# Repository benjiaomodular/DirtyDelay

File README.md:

# DirtyDelay
A PT2399-based delay guitar pedal with an overdrive at the output

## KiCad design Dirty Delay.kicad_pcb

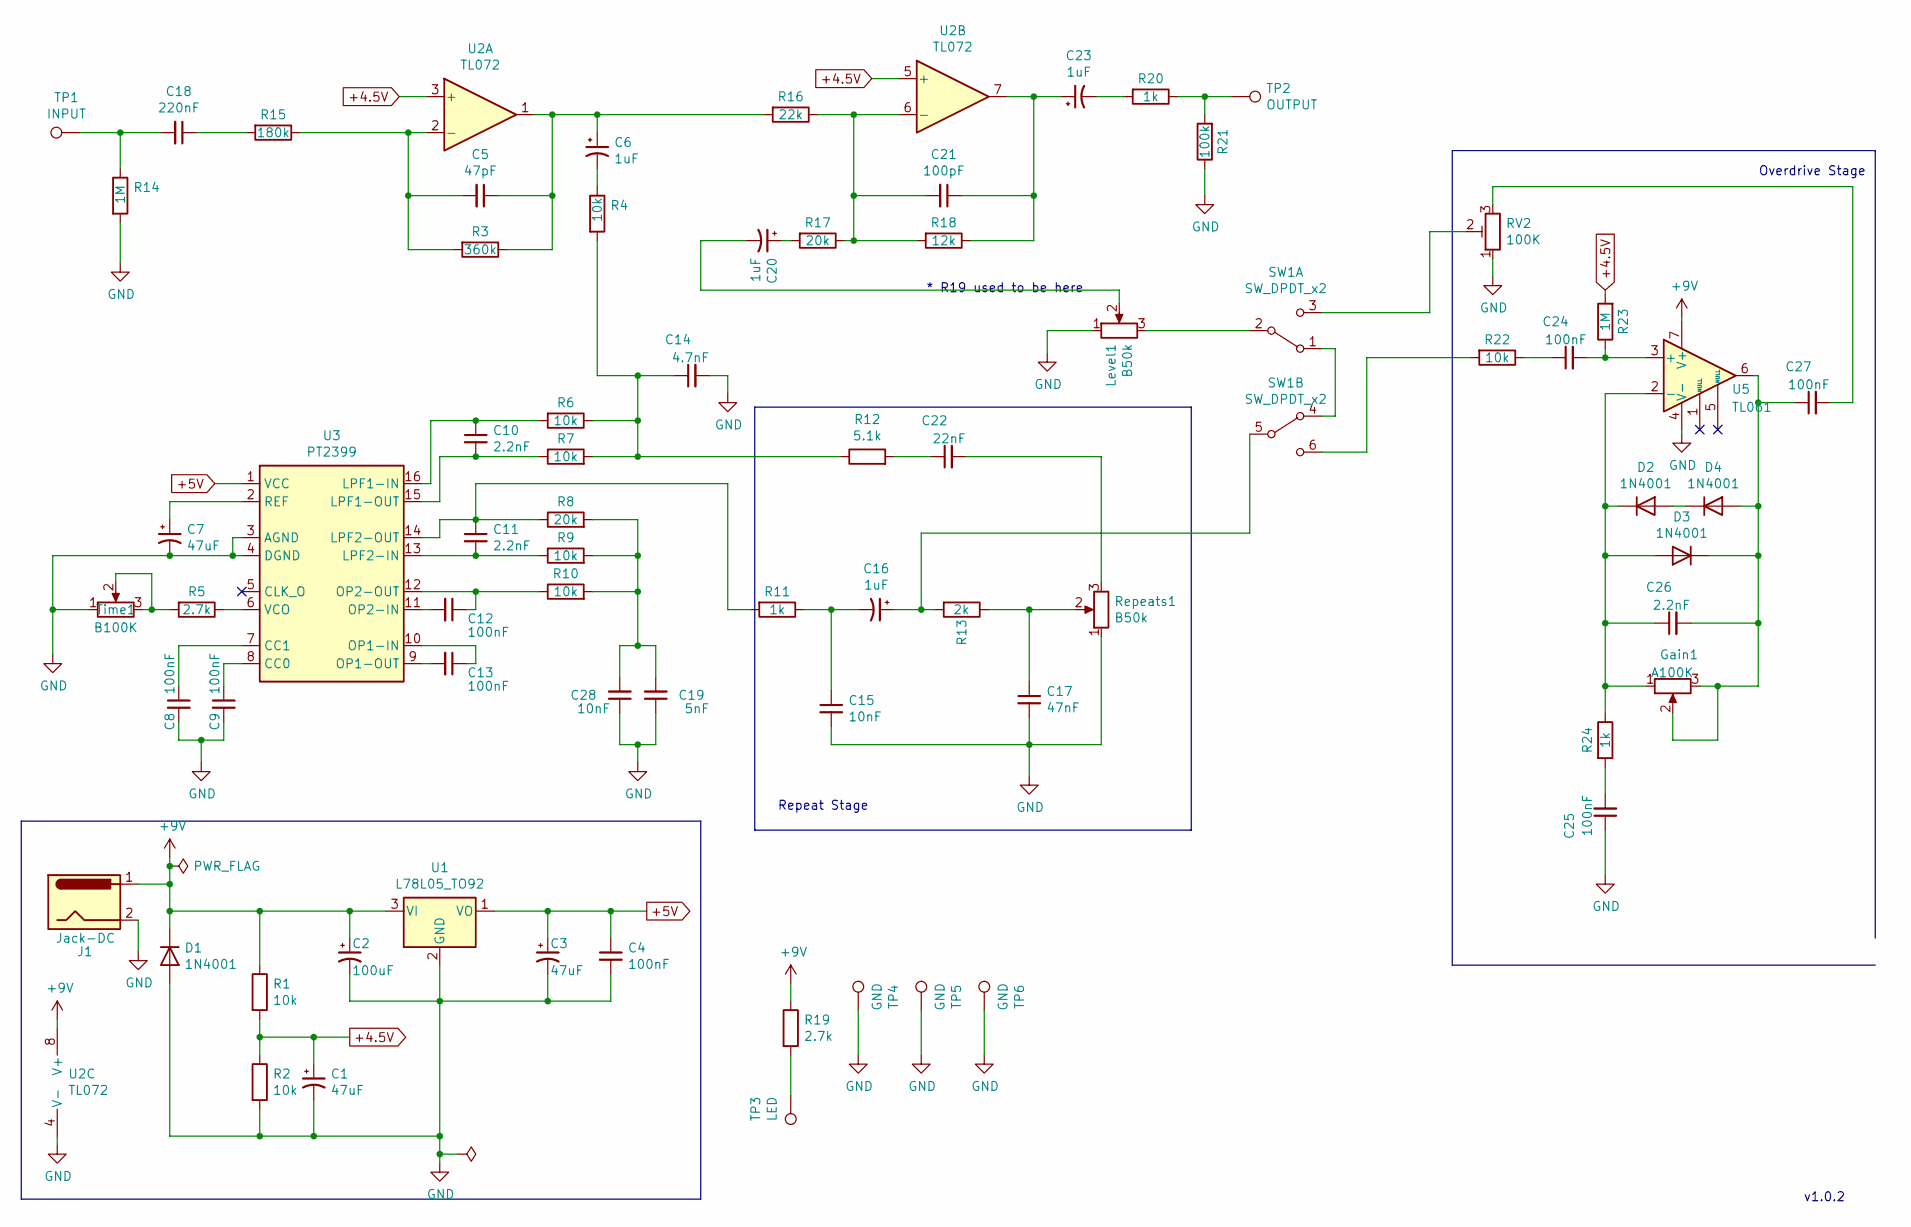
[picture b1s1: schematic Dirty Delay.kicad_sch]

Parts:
C1, C3, C7: 47uF; CP_Radial_D5.0mm_P2.50mm
C2: 100uF; CP_Radial_D6.3mm_P2.50mm
C4, C8, C9, C12, C13, C24, C25, C27: 100nF; C_Disc_D5.0mm_W2.5mm_P2.50mm
C5: 47pF; C_Disc_D5.0mm_W2.5mm_P2.50mm
C6, C16, C20, C23: 1uF; CP_Radial_D4.0mm_P1.50mm
C10, C11, C26: 2.2nF; C_Disc_D5.0mm_W2.5mm_P2.50mm
C14: 4.7nF; C_Rect_L7.0mm_W3.5mm_P5.00mm
C15, C28: 10nF; C_Disc_D5.0mm_W2.5mm_P2.50mm
C17: 47nF; C_Disc_D5.0mm_W2.5mm_P2.50mm
C18: 220nF; C_Rect_L13.0mm_W8.0mm_P10.00mm_FKS3_FKP3_MKS4
C19: 5nF; C_Disc_D5.0mm_W2.5mm_P2.50mm
C21: 100pF; C_Disc_D5.0mm_W2.5mm_P2.50mm
C22: 22nF; C_Disc_D5.0mm_W2.5mm_P2.50mm
D1, D2, D3, D4: 1N4001; D_DO-41_SOD81_P10.16mm_Horizontal
Gain1: A100K; SolderWire-0.5sqmm_1x03_P4.8mm_D0.9mm_OD2.3mm
J1: Jack-DC; SolderWire-0.5sqmm_1x02_P4.8mm_D0.9mm_OD2.3mm
Level1: B50k; SolderWire-0.5sqmm_1x03_P4.8mm_D0.9mm_OD2.3mm
R1, R2, R4, R6, R7, R9, R10, R22: 10k; R_Axial_DIN0207_L6.3mm_D2.5mm_P7.62mm_Horizontal
R3: 360k; R_Axial_DIN0207_L6.3mm_D2.5mm_P7.62mm_Horizontal
R5, R19: 2.7k; R_Axial_DIN0207_L6.3mm_D2.5mm_P7.62mm_Horizontal
R8, R17: 20k; R_Axial_DIN0207_L6.3mm_D2.5mm_P7.62mm_Horizontal
R11, R20, R24: 1k; R_Axial_DIN0207_L6.3mm_D2.5mm_P7.62mm_Horizontal
R12: 5.1k; R_Axial_DIN0207_L6.3mm_D2.5mm_P7.62mm_Horizontal
R13: 2k; R_Axial_DIN0207_L6.3mm_D2.5mm_P7.62mm_Horizontal
R14, R23: 1M; R_Axial_DIN0207_L6.3mm_D2.5mm_P7.62mm_Horizontal
R15: 180k; R_Axial_DIN0207_L6.3mm_D2.5mm_P7.62mm_Horizontal
R16: 22k; R_Axial_DIN0207_L6.3mm_D2.5mm_P7.62mm_Horizontal
R18: 12k; R_Axial_DIN0207_L6.3mm_D2.5mm_P7.62mm_Horizontal
R21: 100k; R_Axial_DIN0207_L6.3mm_D2.5mm_P7.62mm_Horizontal
RV2: 100K; Potentiometer_Bourns_3296W_Vertical
Repeats1: B50k; SolderWire-0.5sqmm_1x03_P4.8mm_D0.9mm_OD2.3mm
SW1: SW_DPDT_x2; SolderWire-0.5sqmm_1x06_P4.8mm_D0.9mm_OD2.3mm
TP1: INPUT; SolderWire-0.5sqmm_1x01_D0.9mm_OD2.3mm
TP2: OUTPUT; SolderWire-0.5sqmm_1x01_D0.9mm_OD2.3mm
TP3: LED; SolderWire-0.5sqmm_1x01_D0.9mm_OD2.3mm
TP4, TP5, TP6: GND; SolderWire-0.5sqmm_1x01_D0.9mm_OD2.3mm
Time1: B100K; SolderWire-0.5sqmm_1x03_P4.8mm_D0.9mm_OD2.3mm
U1: L78L05_TO92; TO-92_Inline
U2: TL072; DIP-8_W7.62mm_Socket_LongPads
U3: PT2399; DIP-16_W7.62mm_Socket_LongPads
U5: TL061; DIP-8_W7.62mm_Socket_LongPads

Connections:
+4.5V: C1.1, R1.2, R2.1, R23.2, U2.3 (+), U2.5 (+)
+5V: C3.1, C4.1, U1.1 (VO), U3.1 (VCC)
+9V: C2.1, D1.1 (K), J1.1, R1.1, R19.1, U1.3 (VI), U2.8 (V+), U5.7 (V+)
GND: C1.2, C2.2, C3.2, C4.2, C7.2, C8.2, C9.2, C14.2, C15.2, C17.2, C19.1, C25.1, C28.1, D1.2 (A), J1.2, Level1.1, R2.2, R14.2, R21.1, RV2.1, Repeats1.1, TP4.1, TP5.1, TP6.1, Time1.1, U1.2 (GND), U2.4 (V-), U3.3 (AGND), U3.4 (DGND), U5.4 (V-); also elsewhere on the board
unnamed: C5.1, C6.1, R3.1, R16.2, U2.1
unnamed: C5.2, R3.2, R15.1, U2.2 (-)
unnamed: C6.2, R4.1
unnamed: C7.1, U3.2 (REF)
unnamed: C8.1, U3.7 (CC1)
unnamed: C9.1, U3.8 (CC0)
unnamed: C10.1, R6.2, U3.16 (LPF1-IN)
unnamed: C10.2, R7.1, U3.15 (LPF1-OUT)
unnamed: C11.1, R8.1, R11.2, U3.14 (LPF2-OUT)
unnamed: C11.2, R9.1, U3.13 (LPF2-IN)
unnamed: C12.1, R10.1, U3.12 (OP2-OUT)
unnamed: C12.2, U3.11 (OP2-IN)
unnamed: C13.1, U3.10 (OP1-IN)
unnamed: C13.2, U3.9 (OP1-OUT)
unnamed: C14.1, R4.2, R6.1, R7.2, R12.1
unnamed: C15.1, C16.2, R11.1
unnamed 20: C16.1, R13.2, SW1.5 (B); also elsewhere on the board
unnamed: C17.1, R13.1, Repeats1.2
unnamed: C18.1, R15.2
unnamed: C18.2, R14.1, TP1.1
unnamed: C19.2, C28.2, R8.2, R9.2, R10.2
unnamed: C20.1, R17.2
unnamed: C20.2, Level1.2
unnamed: C21.1, C23.1, R18.1, U2.7
unnamed: C21.2, R16.1, R17.1, R18.2, U2.6 (-)
unnamed: C22.1, R12.2
unnamed: C22.2, Repeats1.3
unnamed: C23.2, R20.2
unnamed: C24.1, R22.1
unnamed: C24.2, R23.1, U5.3 (+)
unnamed: C25.2, R24.2
unnamed: C26.1, D2.1 (K), D3.2 (A), Gain1.1, R24.1, U5.2 (-)
unnamed: C26.2, C27.1, D3.1 (K), D4.2 (A), Gain1.2, Gain1.3, U5.6
unnamed 37: C27.2, RV2.3; also elsewhere on the board
unnamed: D2.2 (A), D4.1 (K)
unnamed 39: Level1.3, SW1.2 (B); also elsewhere on the board
unnamed: R5.1, U3.6 (VCO)
unnamed: R5.2, Time1.2, Time1.3
unnamed: R19.2, TP3.1
unnamed: R20.1, R21.2, TP2.1
unnamed 44: R22.2, SW1.6 (C); also elsewhere on the board
unnamed 45: RV2.2, SW1.3 (C); also elsewhere on the board
unnamed 46: SW1.1 (A), SW1.4 (A); also elsewhere on the board

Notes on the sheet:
Overdrive Stage
v1.0.2
Repeat Stage
* R19 used to be here

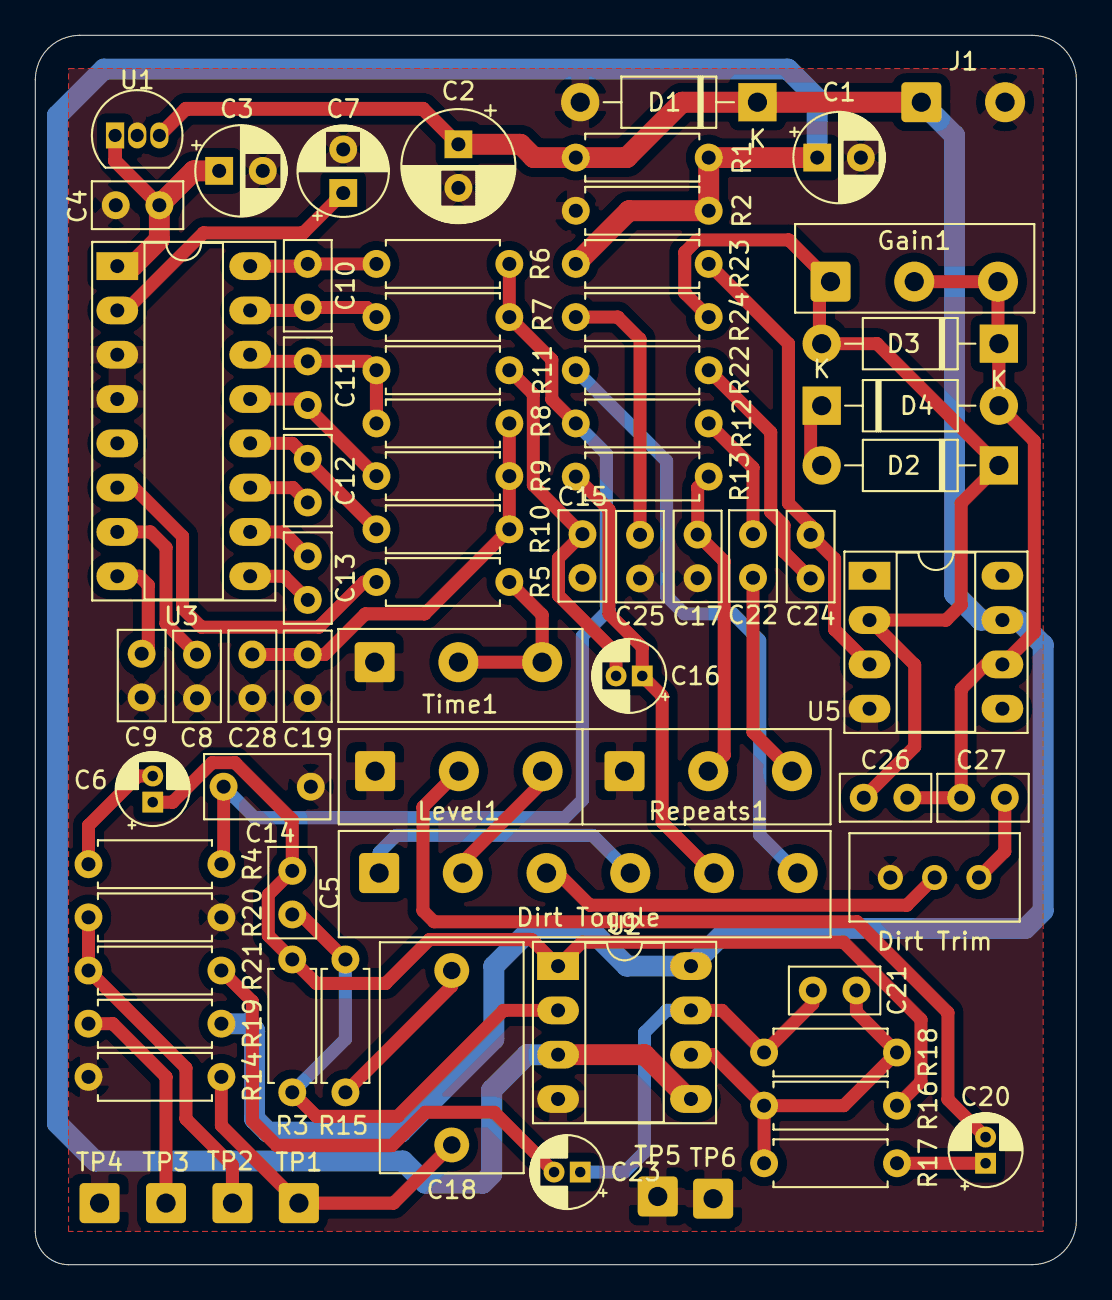
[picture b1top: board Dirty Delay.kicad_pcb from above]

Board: 2 copper layers, 59.7 x 70.5 mm, 73 parts (0 on the bottom side), 47 nets.

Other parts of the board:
Dirt Toggle: SW_DPDT_x2; SolderWire-0.5sqmm_1x06_P4.8mm_D0.9mm_OD2.3mm
Dirt Trim: 100K; Potentiometer_Bourns_3296W_Vertical

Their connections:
GND: Dirt Trim.1; also elsewhere on the board
unnamed 20: Dirt Toggle.5; also elsewhere on the board
unnamed 37: Dirt Trim.3; also elsewhere on the board
unnamed 39: Dirt Toggle.2; also elsewhere on the board
unnamed 44: Dirt Toggle.6; also elsewhere on the board
unnamed 45: Dirt Toggle.3, Dirt Trim.2; also elsewhere on the board
unnamed 46: Dirt Toggle.1, Dirt Toggle.4; also elsewhere on the board

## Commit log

2020-10-17 helo git
2022-11-16 Before github push
2023-03-26 Exported schematics for v1.0.2
2023-03-26 Added license
